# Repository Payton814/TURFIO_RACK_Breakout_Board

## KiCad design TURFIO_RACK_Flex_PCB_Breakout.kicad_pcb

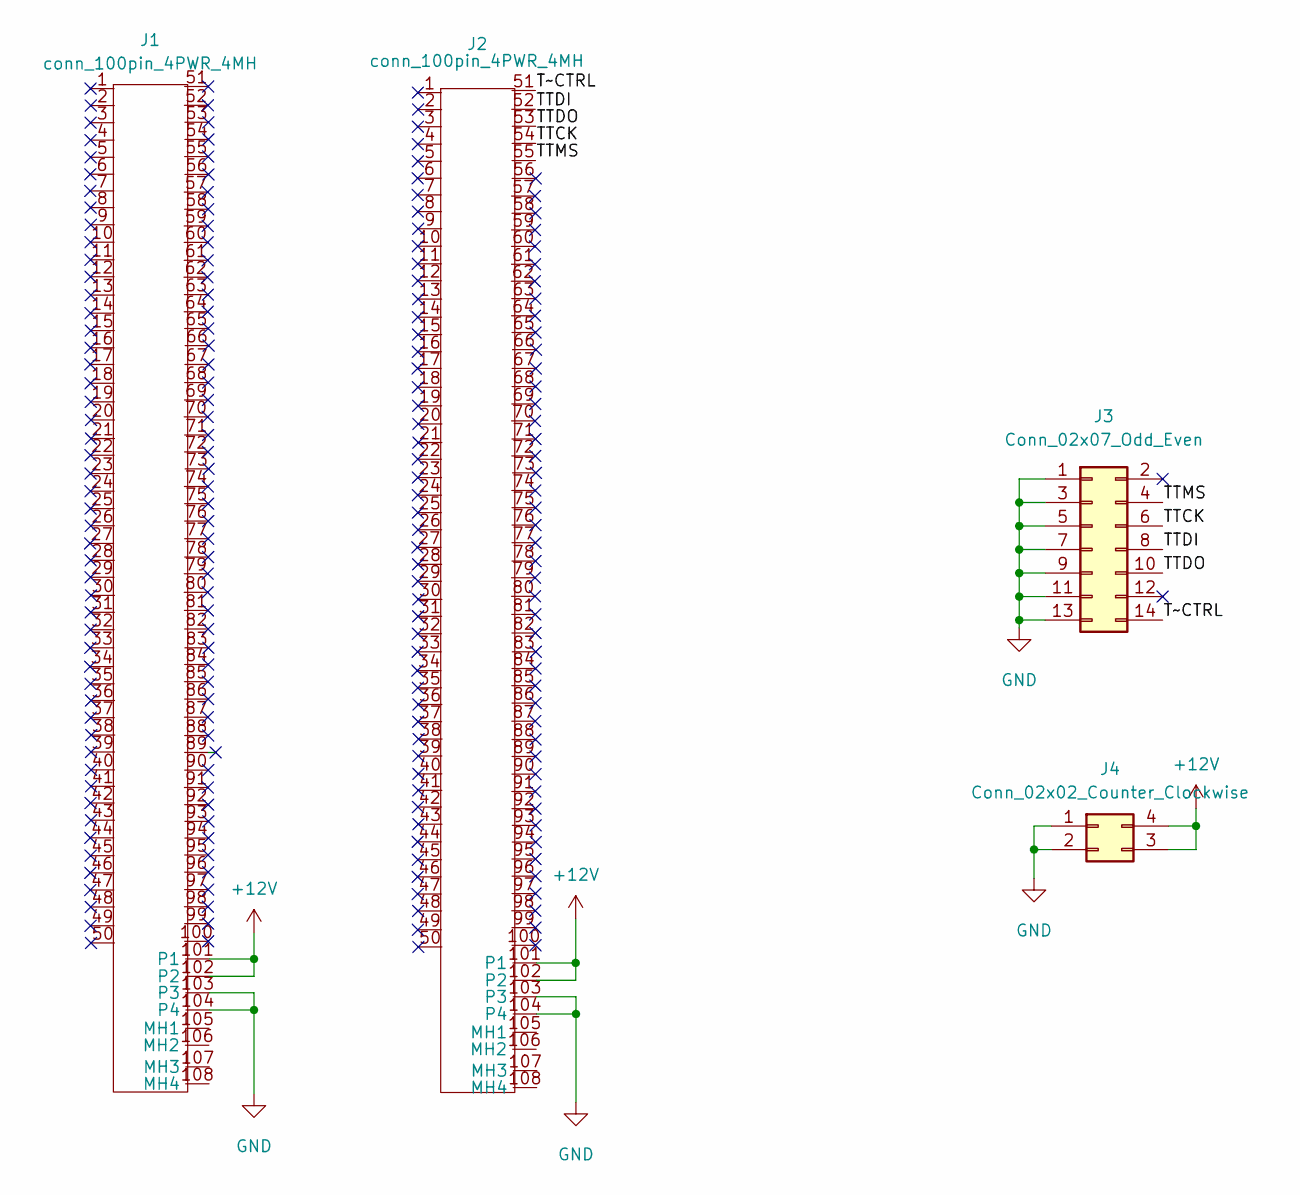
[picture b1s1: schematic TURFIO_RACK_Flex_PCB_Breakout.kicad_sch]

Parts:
J1, J2: conn_100pin_4PWR_4MH; FX23-100P-0.5SV15
J3: Conn_02x07_Odd_Even; PinHeader_2x07_P2.00mm_Vertical
J4: Conn_02x02_Counter_Clockwise; Molex_Mini-Fit_Jr_5569-04A2_2x02_P4.20mm_Horizontal

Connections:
+12V: J1.101 (P1), J1.102 (P2), J2.101 (P1), J2.102 (P2), J4.3, J4.4
/TTCK: J2.54, J3.6
/TTDI: J2.52, J3.8
/TTDO: J2.53, J3.10
/TTMS: J2.55, J3.4
/T~CTRL: J2.51, J3.14
GND: J1.103 (P3), J1.104 (P4), J2.103 (P3), J2.104 (P4), J3.1, J3.3, J3.5, J3.7, J3.9, J3.11, J3.13, J4.1, J4.2

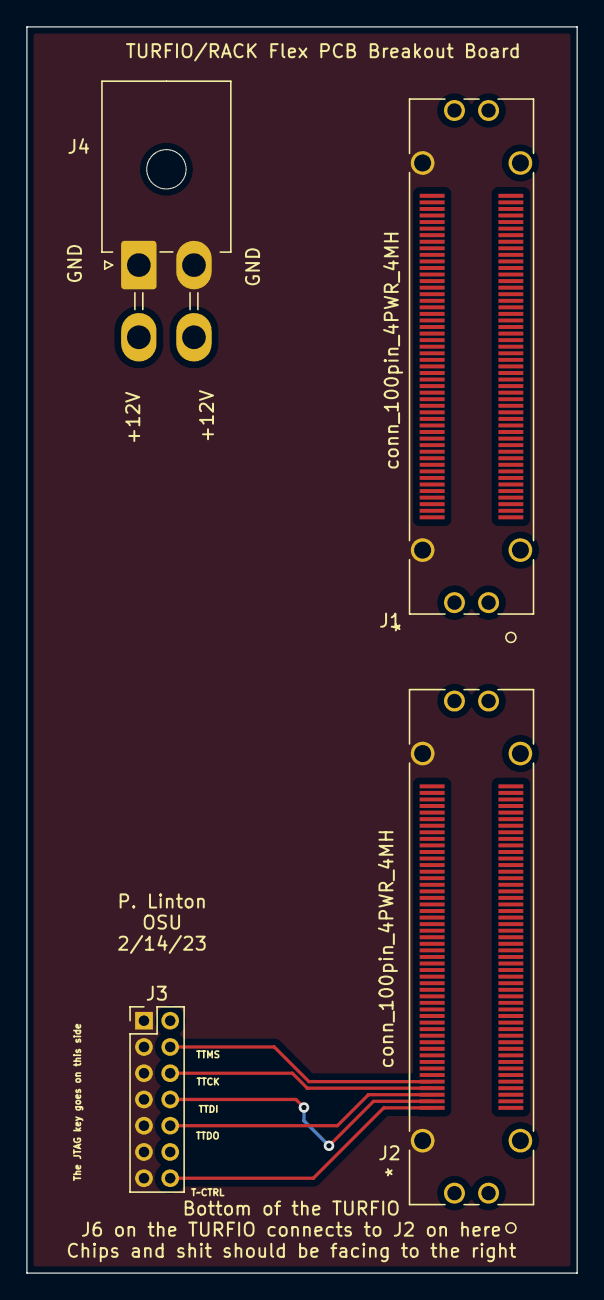
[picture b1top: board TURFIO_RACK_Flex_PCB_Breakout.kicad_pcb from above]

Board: 2 copper layers, 41.9 x 95.0 mm, 5 parts (0 on the bottom side), 7 nets.

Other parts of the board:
John Beacom: LOGO; beacom_silkscreen_negative_v1

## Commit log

2023-02-14 breakout board

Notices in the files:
parts and their libraries:
Copyright 2021 Accelerated Designs. All rights reserved.
